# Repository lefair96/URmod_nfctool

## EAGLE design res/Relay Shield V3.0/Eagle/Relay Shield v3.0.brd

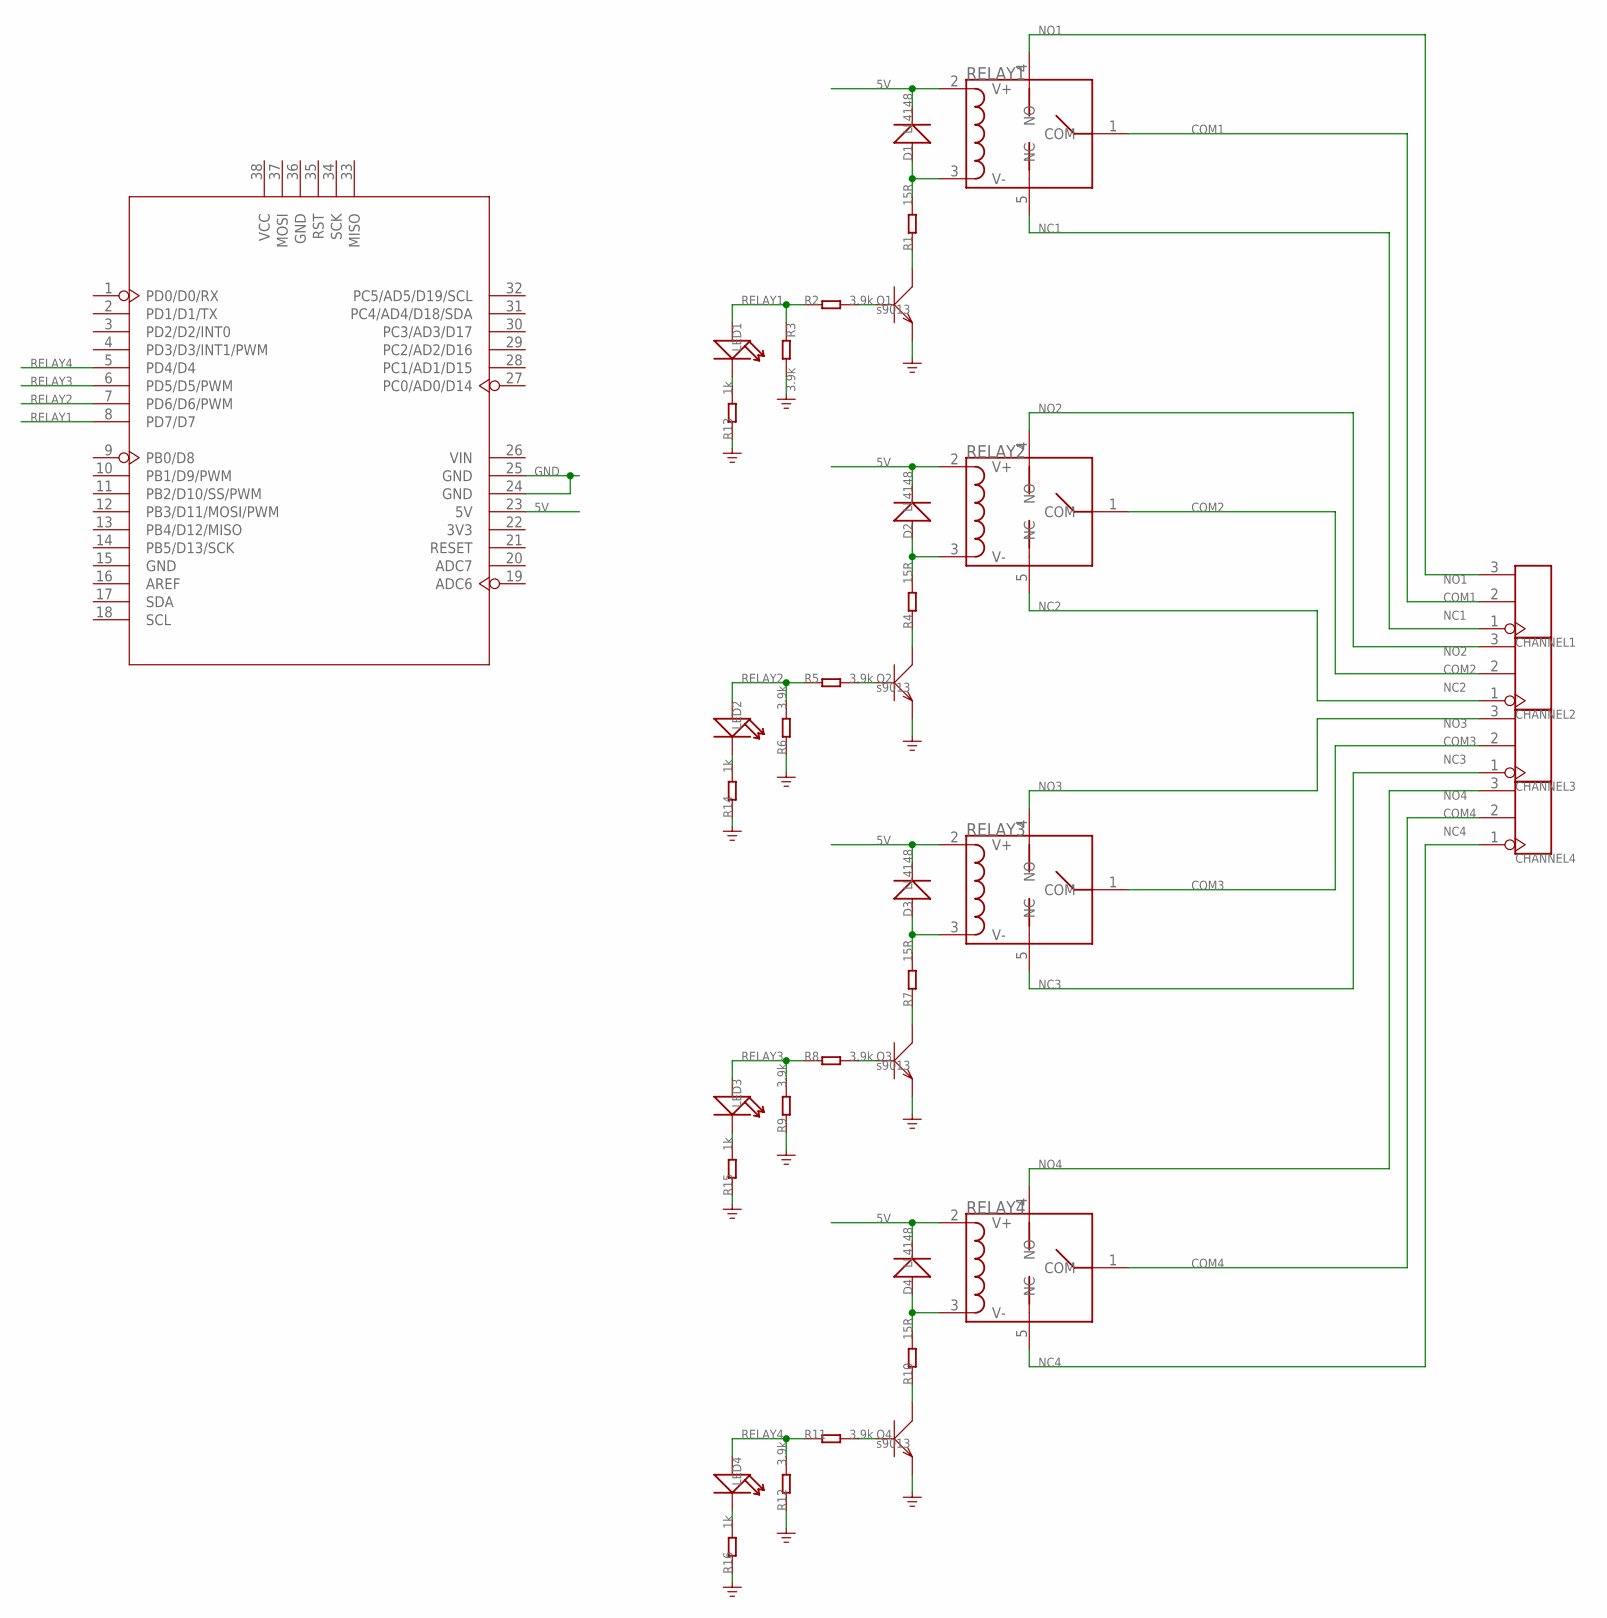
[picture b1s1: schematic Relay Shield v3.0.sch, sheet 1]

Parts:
CHANNEL1, CHANNEL2, CHANNEL3, CHANNEL4: SCREW-TERMINAL-3P'3.5'; 3P-3.5
D1, D2, D3, D4: LL4148; LL-34
LED1, LED2, LED3, LED4: LED'0603'; LED-0603
Q1, Q2, Q3, Q4: s9013; SOT23
R1, R4, R7, R10: 15R; R0603
R2, R3, R5, R6, R8, R9, R11, R12: 3.9k; R0603
R13, R14, R15, R16: 1k; R0603
RELAY1, RELAY2, RELAY3, RELAY4: RELAY-HLS8L-DC5V-S-C; 5P-19.0X15.5X15.8H
U2: ARDUINO-38P; ARDUINO-38P-WITH/-SILK-500519002

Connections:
5V: D1.C (-), D2.C (-), D3.C (-), D4.C (-), RELAY1.2 (V+), RELAY2.2 (V+), RELAY3.2 (V+), RELAY4.2 (V+), U2.23 (5V)
COM1: CHANNEL1.2, RELAY1.1 (COM)
COM2: CHANNEL2.2, RELAY2.1 (COM)
COM3: CHANNEL3.2, RELAY3.1 (COM)
COM4: CHANNEL4.2, RELAY4.1 (COM)
GND: Q1.2 (E), Q2.2 (E), Q3.2 (E), Q4.2 (E), R3.2, R6.1, R9.1, R12.1, R13.1, R14.1, R15.1, R16.1, U2.24 (GND), U2.25 (GND)
unnamed: D2.A (+), R4.2, RELAY2.3 (V-)
unnamed: D3.A (+), R7.2, RELAY3.3 (V-)
unnamed: D4.A (+), R10.2, RELAY4.3 (V-)
unnamed: Q1.3 (C), R1.1
unnamed: Q2.3 (C), R4.1
unnamed: Q4.1 (B), R11.2
unnamed: D1.A (+), R1.2, RELAY1.3 (V-)
unnamed: Q3.3 (C), R7.1
unnamed: Q4.3 (C), R10.1
unnamed: Q3.1 (B), R8.2
unnamed: LED1.-, R13.2
unnamed: LED2.-, R14.2
unnamed: LED3.-, R15.2
unnamed: LED4.-, R16.2
unnamed: Q2.1 (B), R5.2
unnamed: Q1.1 (B), R2.2
NC1: CHANNEL1.1, RELAY1.5 (NC)
NC2: CHANNEL2.1, RELAY2.5 (NC)
NC3: CHANNEL3.1, RELAY3.5 (NC)
NC4: CHANNEL4.1, RELAY4.5 (NC)
NO1: CHANNEL1.3, RELAY1.4 (NO)
NO2: CHANNEL2.3, RELAY2.4 (NO)
NO3: CHANNEL3.3, RELAY3.4 (NO)
NO4: CHANNEL4.3, RELAY4.4 (NO)
RELAY1: LED1.+, R2.1, R3.1, U2.8 (PD7/D7)
RELAY2: LED2.+, R5.1, R6.2, U2.7 (PD6/D6/PWM)
RELAY3: LED3.+, R8.1, R9.2, U2.6 (PD5/D5/PWM)
RELAY4: LED4.+, R11.1, R12.2, U2.5 (PD4/D4)

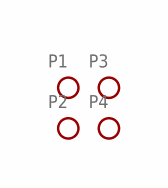
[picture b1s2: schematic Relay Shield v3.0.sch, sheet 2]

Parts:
P1, P2, P3, P4: PAD-MARK; ROUND-MARK-1.0

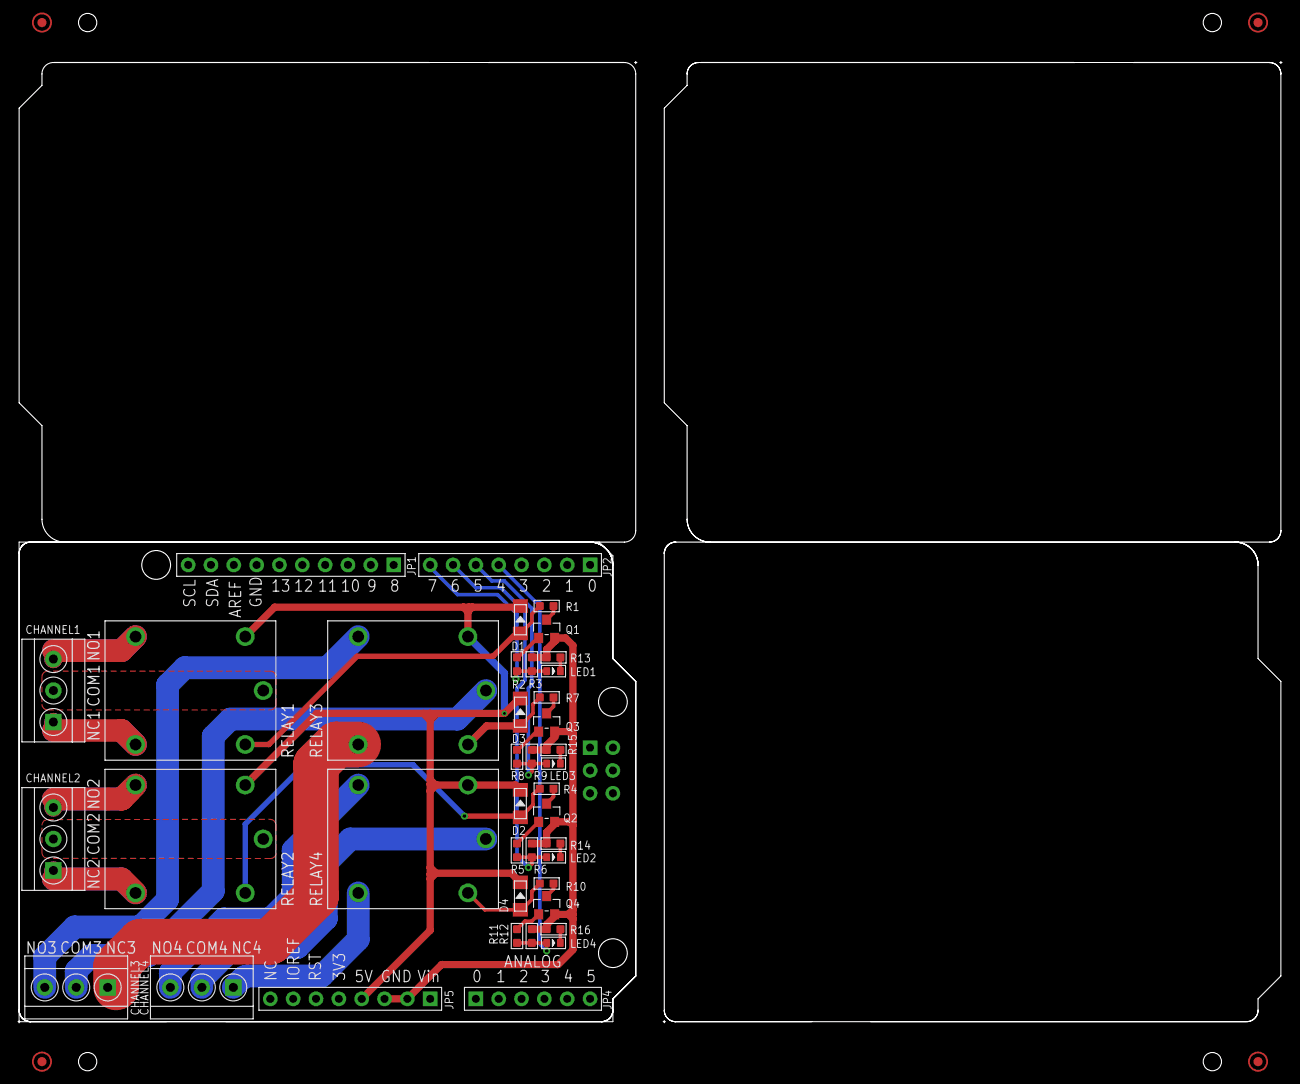
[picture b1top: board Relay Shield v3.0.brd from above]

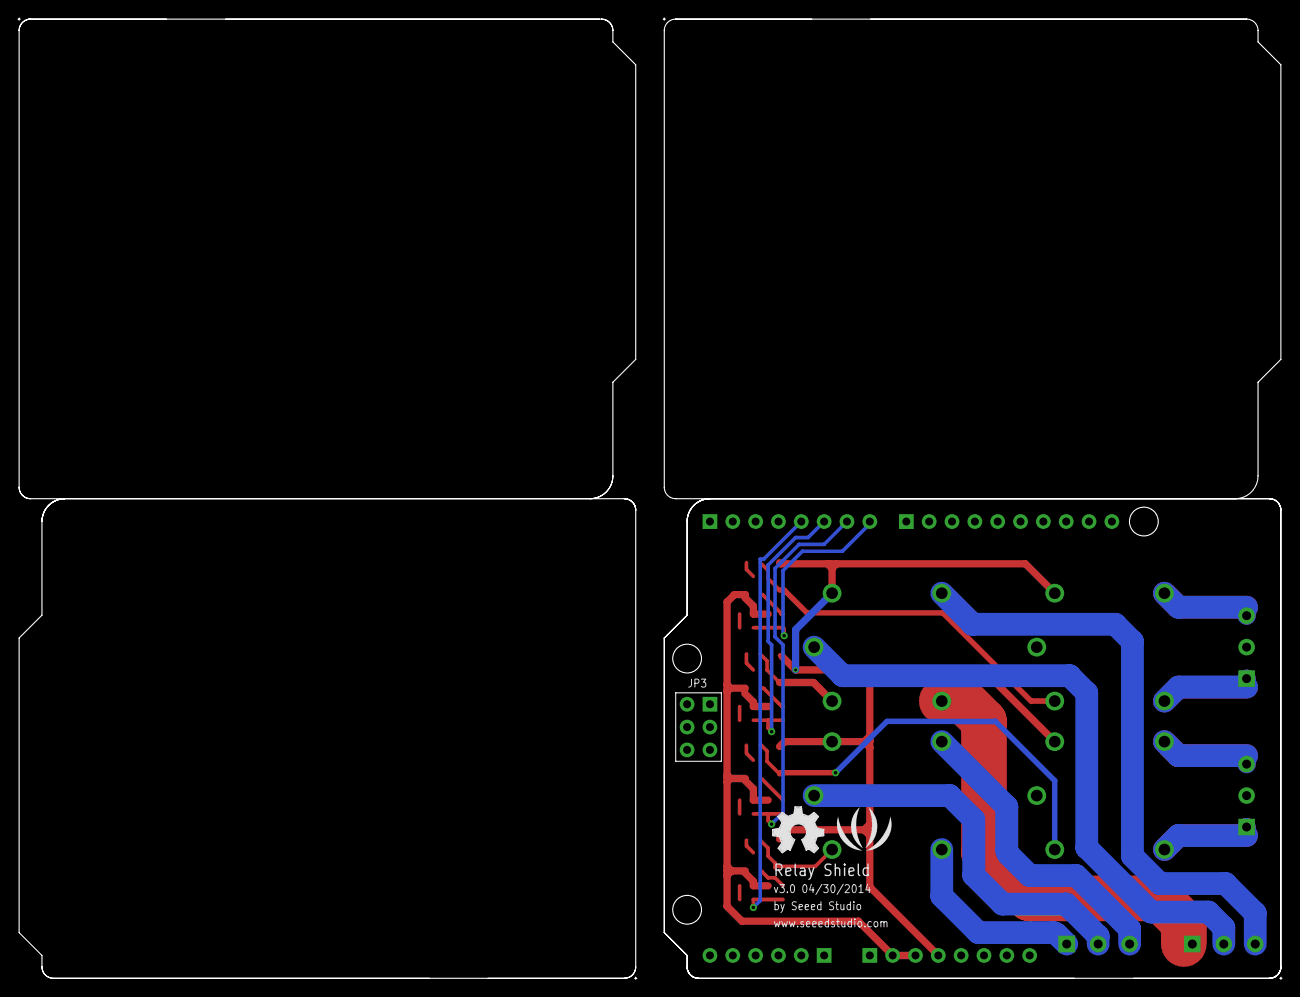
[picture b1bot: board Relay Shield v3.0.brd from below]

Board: 2 copper layers, 140.6 x 106.9 mm, 43 parts (2 on the bottom side), 34 nets.

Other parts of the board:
U$13: LOGO_SILK
U$14: OSHW_FILLX200_NOTEXT

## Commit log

2021-09-13 added platform.io dependency
2021-09-13 added nfc library and program
2021-09-22 added adafruit shield library
2021-09-22 renamed adafruit lib, backedup previous main program
2021-09-22 edited main with readmifare example as in https://learn.adafruit.com/adafruit-pn532-rfid-nfc/arduino-library
2021-09-22 added code for activation of relays, added schematics of relay shield
2021-09-22 added arbitrary cycle time delay
2021-09-22 added resources for the antenna shield
2021-09-22 added Fritzing Scheme
2021-09-22 updated scheme with UR control box interface
2021-09-22 added status feedback signal
2021-09-22 added vs code management
2021-10-11 added urscript folder
2021-10-11 added robot scripts
